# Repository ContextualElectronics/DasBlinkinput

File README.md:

# DasBlinkinput
A light detection system that is part of the Roll With It project for Contextual Electronics.

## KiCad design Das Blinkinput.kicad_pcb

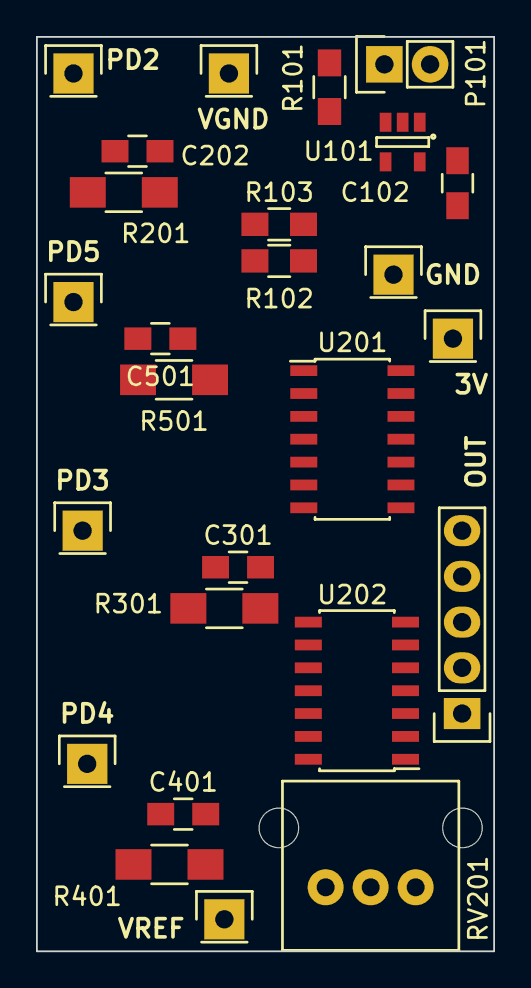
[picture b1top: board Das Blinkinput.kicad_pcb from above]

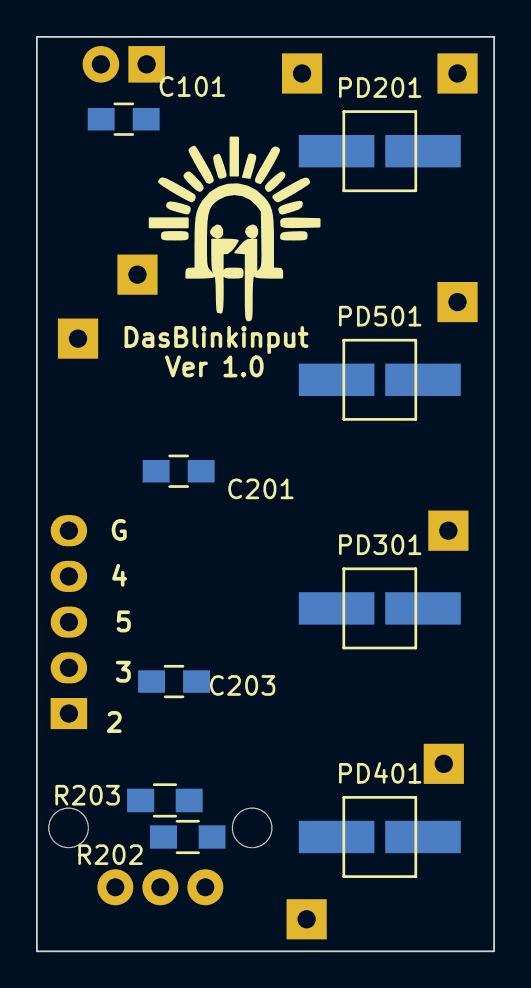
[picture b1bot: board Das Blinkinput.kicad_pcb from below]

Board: 4 copper layers, 25.4 x 50.8 mm, 35 parts (9 on the bottom side), 19 nets, no tracks yet.

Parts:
C101, C102: 1U; C_0805_HandSoldering
C201, C203: .1U; C_0805_HandSoldering
C202, C301, C401, C501: 100p; C_0805_HandSoldering
P101: CONN_01X02; Pin_Header_Straight_1x02
P102, P103, P104, P106, P201, P301, P401, P501: CONN_01X01; Pin_Header_Straight_1x01
P105: CONN_01X05; Pin_Header_Straight_1x05
PD201, PD301, PD401, PD501: VBPW34SR; VPW34SR*
R101: 0; R_0805_HandSoldering
R102, R103, R202, R203: 10K; R_0805_HandSoldering
R201, R301, R401, R501: 1MEG; R_1206_HandSoldering
RV201: POT; P090L-02F25BR10K
U101: LP2980IM5-3.0/NOPB; SOT-23-5
U201: MCP6404; SOIC-14_3.9x8.7mm_Pitch1.27mm
U202: LM339; SOIC-14_3.9x8.7mm_Pitch1.27mm

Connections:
3V: C102.1, C201.2, C203.2, P103.1, R102.1, R203.2, U101.5, U201.4, U202.3
/Channel1Photodetect/PD2: P105.1, U202.1
/Channel2Photodetect/PD3: P105.2, U202.14
/Channel2Photodetect/REF_IN: P106.1, R202.2, RV201.3, U202.4, U202.6, U202.8, U202.10
/Channel3Photodetect/PD5: P105.3, U202.2
/Channel4Photodetect/PD4: P105.4, U202.13
GND: C101.2, C102.2, C201.1, C203.1, P101.1, P104.1, P105.5, R101.2, R103.2, R202.1, U101.2, U201.11, U202.12
unnamed: C101.1, P101.2, U101.1
unnamed: C202.1, P201.1, R201.1, U201.14, U202.7
unnamed: C202.2, PD201.2, R201.2, U201.13
unnamed: C301.1, P301.1, R301.1, U201.8, U202.9
unnamed: C301.2, PD301.2, R301.2, U201.9
unnamed: C401.1, P401.1, R401.1, U201.7, U202.11
unnamed: C401.2, PD401.2, R401.2, U201.6
unnamed: C501.1, P501.1, R501.1, U201.1, U202.5
unnamed: C501.2, PD501.2, R501.2, U201.2
unnamed: R101.1, U101.3
unnamed: R203.1, RV201.2
VGND: P102.1, PD201.1, PD301.1, PD401.1, PD501.1, R102.2, R103.1, U201.3, U201.5, U201.10, U201.12

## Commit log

2015-05-04 Added initial board outline based around the size of a Droid RAZR MAXX
2015-05-10 Added the simulation file being used in the early videos
2015-05-11 Adjusted the screen outline from vertical to horizontal
2015-05-11 Added schematic with preliminary components and a new library for schematic symbols
2015-05-13 Added part numbers and links to schematic
2015-05-13 Updated the simulation to run AC analysis with the bypass capacitor
2015-05-13 Channelizing the DB circuits
2015-05-15 Added power regulator, VGND and test points
2015-05-15 Added libraries and imported components into the layout
2015-05-18 Added photodiode component to new local footprint library
2015-05-18 Added secondary footprint for photodiode
2015-05-18 Removing extra set of photodiodes and changing the original photodiode footprint
2015-05-18 Schematic and layout cleanup after photodiode removal
2015-05-23 Increased board size to 2 sq inches and layer count to 4
2015-05-23 Did power layout and began op amp connection
2015-05-23 Routed all passives related to U201 and the photodiodes
2015-05-23 Routed remainder of lines and added test points with lables
2015-05-23 Connected REF_IN Test Point
2015-05-24 Moved potentiometer and output pins
2015-05-24 Added CE logo and did DRC
2015-05-25 Changed potentiometer NPTH drills and generated Gerbers
2015-05-25 Revised Gerber extensions and sent v1.0 to fab
2015-06-02 Added CSV via BOM dialog in eeSchema for manufacturing
2015-06-02 Changed linear regulator to list full part number in MPN field.
2015-06-03 Created DB-CB branch by removing all traces
